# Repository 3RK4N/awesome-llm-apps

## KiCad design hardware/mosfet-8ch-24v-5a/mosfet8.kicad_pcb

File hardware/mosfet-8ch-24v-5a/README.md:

# 8 Kanal 24 V PNP MOSFET Çıkış Kartı (NPN/PNP girişli, DIN ray)

PLC / kontrol kartı çıkışlarını yükselten, opto-izoleli 8 kanallı high-side
(PNP, kaynak tipi) MOSFET kartı. Her giriş kendi çıkışını sürer; kartta işlemci yoktur.

## Özellikler

| | |
|---|---|
| Besleme | 24 V DC (19–30 V) |
| Çıkış | 8 × 24 V PNP, kanal başına 5 A sürekli |
| Toplam akım | 20 A (70 µm / 2 oz bakır ile); 35 µm bakırda 12 A ile sınırlayın |
| Giriş | 8 × 24 V, JP1 ile NPN veya PNP; ~3,7 mA @ 24 V, açma eşiği yaklaşık 7–9 V |
| İzolasyon | Giriş–çıkış arası optokuplör (JP1 takılı değilken ve `COM` ayrı beslenirken) |
| Koruma | Kanal başına 7 A hızlı SMD sigorta, serbest geçiş diyodu, kapı zeneri; beslemede TVS |
| Gösterge | Kanal başına yeşil LED (kapı sürülürken yanar), mavi besleme LED'i |
| PCB | 62 × 72 mm, 2 katman, tek yüz SMD dizgi |
| Montaj | 72 mm PCB genişliğine uygun DIN ray taşıyıcı (UM72 tipi profil); rayda 62 mm yer kaplar |
| Anahtarlama | Aç/kapa kullanım, en fazla ~20 Hz (PWM için uygun değildir) |

## Bağlantı

- **J3 (üst sağ):** soldan sağa `+24V +24V 0V 0V`. Toplam akım 12 A'yı geçiyorsa iki `+24V` kutbunu da kullanın.
- **J1 (üst sol):** soldan sağa `IN1 … IN8, COM`.
- **J2 (alt):** soldan sağa `OUT1 … OUT8`. Yük `OUTn` ile 0 V arasına bağlanır.
- **JP1:**
  - 1-2 (üst): **NPN** giriş — `COM` = +24 V, giriş 0 V'a çekilince kanal açılır.
  - 2-3 (alt): **PNP** giriş — `COM` = 0 V, girişe +24 V gelince kanal açılır.
  - Jumper yok: `COM` klemensine harici ortak uç bağlanır, giriş tarafı tam izole olur.

## Kanal devresi

```
IN ─ 4k7 ─┬─ opto LED (çift yönlü) ─ COM        +24V ─┬─ 10k ─┬─ ZD 15V ─┐
          └─ 1k ────────────────────┘                 │       │          │
                                                      S     kapı ────────┘
 opto C ─ LED ─ 10k ─ kapı        opto E ─ 0V       P-MOSFET
                                                      D ─ sigorta 7A ─┬─ OUT
                                                                      └─ SS36 ─ 0V
```

24 V'ta kapı gerilimi yaklaşık −11 V olur. SUD50P06-15 için iletim direnci en fazla
15 mΩ (25 °C); 5 A'da kanal başına yaklaşık 0,4–0,6 W ısı çıkar.

## Dosyalar

| Dosya | İçerik |
|---|---|
| `mosfet8.kicad_pro / .kicad_sch / .kicad_pcb` | KiCad 7 projesi (şema + PCB) |
| `mosfet8-schematic.pdf` | Şema çıktısı |
| `bom.csv` | Malzeme listesi (18 kalem, 88 parça) |
| `gerber/` | Gerber, delik (Excellon) ve dizgi konum dosyaları |
| `docs/` | PCB önizleme görselleri |
| `scripts/` | Şemayı ve PCB'yi üreten betikler |

Tasarım `scripts/design.py` içindeki tek bir bağlantı tablosundan üretilir. Yeniden üretmek için
(KiCad 7 kurulu Linux'ta):

```bash
cd scripts
python3 gen_sch.py && /usr/bin/python3 gen_pcb.py && python3 gen_bom.py
```

KiCad'de elle düzenleme yaparsanız betikleri tekrar çalıştırmayın; dosyaların üzerine yazar.

## Doğrulama durumu

- Şemadan çıkarılan netlist, bağlantı tablosuyla birebir eşleşiyor (60 net, 88 parça).
- KiCad 7.0.11 DRC: açıklık, kısa devre ve bağlanmamış pad hatası yok. Kalan 88 uyarı,
  betiğin çalıştığı ortamda kılıf kütüphane tablosu olmamasından kaynaklanır.
- ERC çalıştırılmadı (KiCad 7 komut satırında yok); projeyi açınca bir kez ERC çalıştırın.
- **Prototip üretilmedi ve test edilmedi.** Isıl değerler hesap tahminidir.

## Üretimden önce kontrol edilecekler

1. **Parça numaraları** hafızadan yazıldı. Siparişten önce datasheet'ten kılıf, pin sırası ve
   değerleri doğrulayın; özellikle Q (DPAK: 1 = G, tab = D, 3 = S) ve optokuplör (SO-4: 1-2 LED, 3 = E, 4 = C).
2. **Bakır kalınlığı:** 70 µm (2 oz) sipariş edin. 35 µm ile toplam akımı 12 A'da tutun.
3. **Kısa devre:** MOSFET'in kendi akım sınırlaması yoktur; koruma sigortaya ve güç kaynağının
   akım sınırına dayanır. Sigorta atınca değiştirilmesi gerekir (lehimli).
4. **Kanal LED'i** kapının sürüldüğünü gösterir; sigorta atmışsa LED yanar ama çıkış gelmez.
5. **Taşıyıcı:** PCB'de montaj deliği yoktur; kenardan tutan profil taşıyıcı varsayıldı.
   Seçtiğiniz taşıyıcının kenar payını (kenarda en yakın parça ~0,9 mm) kontrol edin.
6. **Klemensler** Phoenix PT 1,5 (3,5 mm) ve MKDS (5,08 mm) ayak izleridir; muadil kullanacaksanız
   ayak aralığı ve pin çapını karşılaştırın.

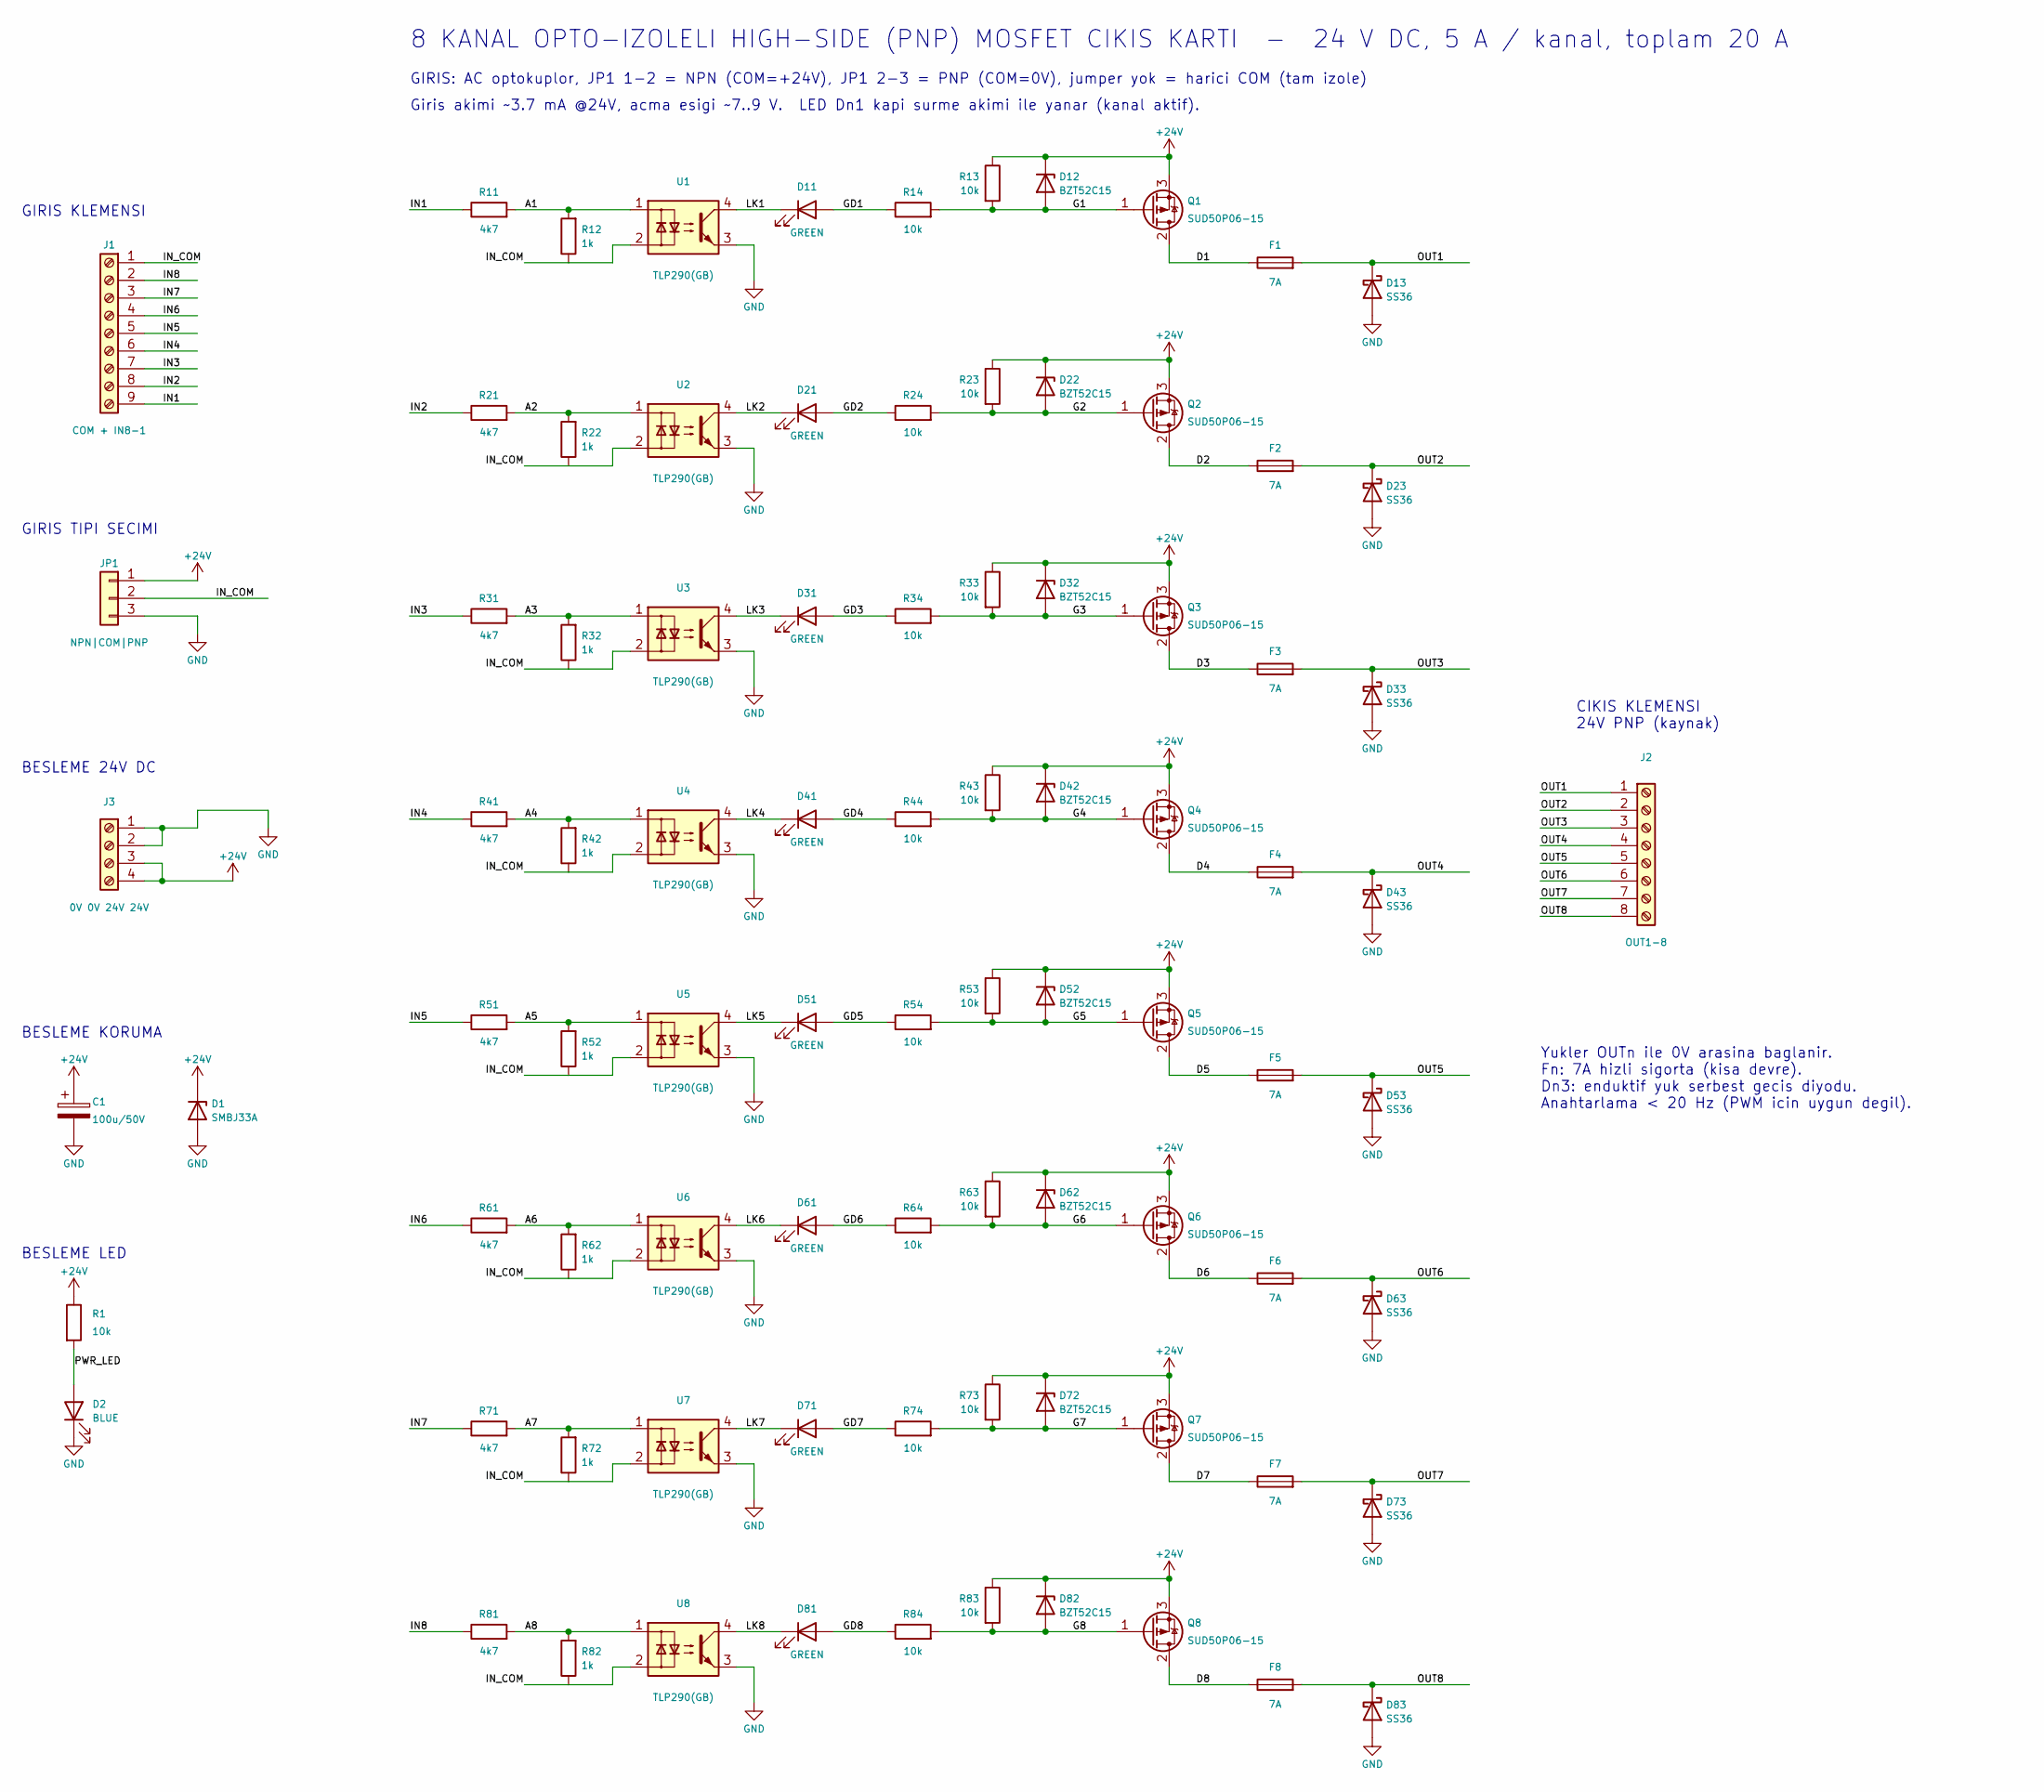
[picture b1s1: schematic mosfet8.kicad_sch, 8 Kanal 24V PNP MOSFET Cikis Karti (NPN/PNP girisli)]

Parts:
C1: 100u/50V; CP_Elec_8x10; MPN EEE-FK1H101P
D1: SMBJ33A; D_SMB; MPN SMBJ33A
D2: BLUE; LED_0603_1608Metric; MPN KP-1608QBC-D / 19-217/BHC
D11, D21, D31, D41, D51, D61, D71, D81: GREEN; LED_0603_1608Metric; MPN KP-1608SGC / 19-217/GHC
D12, D22, D32, D42, D52, D62, D72, D82: BZT52C15; D_SOD-123; MPN BZT52C15-7-F
D13, D23, D33, D43, D53, D63, D73, D83: SS36; D_SMA; MPN SS36
F1, F2, F3, F4, F5, F6, F7, F8: 7A; Fuse_Littelfuse-NANO2-451_453; MPN 0451007.MRL
J1: COM + IN8-1; TerminalBlock_Phoenix_PT-1,5-9-3.5-H_1x09_P3.50mm_Horizontal; MPN PT 1,5/9-3,5-H (1984688)
J2: OUT1-8; TerminalBlock_Phoenix_MKDS-1,5-8-5.08_1x08_P5.08mm_Horizont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; MPN MKDS 1,5/8-5,08 (1715786)
J3: 0V 0V 24V 24V; TerminalBlock_Phoenix_MKDS-3-4-5.08_1x04_P5.08mm_Horizontal; MPN MKDS 3/4-5,08 (1711741)
JP1: NPN|COM|PNP; PinHeader_1x03_P2.54mm_Vertical; MPN Pin header 1x3 2.54mm + jumper
Q1, Q2, Q3, Q4, Q5, Q6, Q7, Q8: SUD50P06-15; TO-252-2; MPN SUD50P06-15-GE3
R1, R13, R14, R23, R24, R33, R34, R43, R44, R53, R54, R63, R64, R73, R74, R83, R84: 10k; R_0603_1608Metric; MPN RC0603FR-0710KL
R11, R21, R31, R41, R51, R61, R71, R81: 4k7; R_1206_3216Metric; MPN RC1206FR-074K7L
R12, R22, R32, R42, R52, R62, R72, R82: 1k; R_0603_1608Metric; MPN RC0603FR-071KL
U1, U2, U3, U4, U5, U6, U7, U8: TLP290(GB); SOP-4_4.4x2.6mm_P1.27mm; MPN TLP290(GB-TP,SE

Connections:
+24V: C1.1, D1.1 (K), D12.1 (K), D22.1 (K), D32.1 (K), D42.1 (K), D52.1 (K), D62.1 (K), D72.1 (K), D82.1 (K), J3.3, J3.4, JP1.1, Q1.3 (S), Q2.3 (S), Q3.3 (S), Q4.3 (S), Q5.3 (S), Q6.3 (S), Q7.3 (S), Q8.3 (S), R1.1, R13.1, R23.1, R33.1, R43.1, R53.1, R63.1, R73.1, R83.1
/A1: R11.2, R12.2, U1.1
/A2: R21.2, R22.2, U2.1
/A3: R31.2, R32.2, U3.1
/A4: R41.2, R42.2, U4.1
/A5: R51.2, R52.2, U5.1
/A6: R61.2, R62.2, U6.1
/A7: R71.2, R72.2, U7.1
/A8: R81.2, R82.2, U8.1
/D1: F1.1, Q1.2 (D)
/D2: F2.1, Q2.2 (D)
/D3: F3.1, Q3.2 (D)
/D4: F4.1, Q4.2 (D)
/D5: F5.1, Q5.2 (D)
/D6: F6.1, Q6.2 (D)
/D7: F7.1, Q7.2 (D)
/D8: F8.1, Q8.2 (D)
/G1: D12.2 (A), Q1.1 (G), R13.2, R14.2
/G2: D22.2 (A), Q2.1 (G), R23.2, R24.2
/G3: D32.2 (A), Q3.1 (G), R33.2, R34.2
/G4: D42.2 (A), Q4.1 (G), R43.2, R44.2
/G5: D52.2 (A), Q5.1 (G), R53.2, R54.2
/G6: D62.2 (A), Q6.1 (G), R63.2, R64.2
/G7: D72.2 (A), Q7.1 (G), R73.2, R74.2
/G8: D82.2 (A), Q8.1 (G), R83.2, R84.2
/GD1: D11.2 (A), R14.1
/GD2: D21.2 (A), R24.1
/GD3: D31.2 (A), R34.1
/GD4: D41.2 (A), R44.1
/GD5: D51.2 (A), R54.1
/GD6: D61.2 (A), R64.1
/GD7: D71.2 (A), R74.1
/GD8: D81.2 (A), R84.1
/IN1: J1.9, R11.1
/IN2: J1.8, R21.1
/IN3: J1.7, R31.1
/IN4: J1.6, R41.1
/IN5: J1.5, R51.1
/IN6: J1.4, R61.1
/IN7: J1.3, R71.1
/IN8: J1.2, R81.1
/IN_COM: J1.1, JP1.2, R12.1, R22.1, R32.1, R42.1, R52.1, R62.1, R72.1, R82.1, U1.2, U2.2, U3.2, U4.2, U5.2, U6.2, U7.2, U8.2
/LK1: D11.1 (K), U1.4
/LK2: D21.1 (K), U2.4
/LK3: D31.1 (K), U3.4
/LK4: D41.1 (K), U4.4
/LK5: D51.1 (K), U5.4
/LK6: D61.1 (K), U6.4
/LK7: D71.1 (K), U7.4
/LK8: D81.1 (K), U8.4
/OUT1: D13.1 (K), F1.2, J2.1
/OUT2: D23.1 (K), F2.2, J2.2
/OUT3: D33.1 (K), F3.2, J2.3
/OUT4: D43.1 (K), F4.2, J2.4
/OUT5: D53.1 (K), F5.2, J2.5
/OUT6: D63.1 (K), F6.2, J2.6
/OUT7: D73.1 (K), F7.2, J2.7
/OUT8: D83.1 (K), F8.2, J2.8
/PWR_LED: D2.2 (A), R1.2
GND: C1.2, D1.2 (A), D2.1 (K), D13.2 (A), D23.2 (A), D33.2 (A), D43.2 (A), D53.2 (A), D63.2 (A), D73.2 (A), D83.2 (A), J3.1, J3.2, JP1.3, U1.3, U2.3, U3.3, U4.3, U5.3, U6.3, U7.3, U8.3

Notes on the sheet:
8 KANAL OPTO-IZOLELI HIGH-SIDE (PNP) MOSFET CIKIS KARTI - 24 V DC, 5 A / kanal, toplam 20 A
GIRIS: AC optokuplor, JP1 1-2 = NPN (COM=+24V), JP1 2-3 = PNP (COM=0V), jumper yok = harici COM (tam izole)
Giris akimi ~3.7 mA @24V, acma esigi ~7..9 V. LED Dn1 kapi surme akimi ile yanar (kanal aktif).
GIRIS KLEMENSI
GIRIS TIPI SECIMI
BESLEME 24V DC
BESLEME KORUMA
BESLEME LED
CIKIS KLEMENSI 24V PNP (kaynak)
Yukler OUTn ile 0V arasina baglanir. Fn: 7A hizli sigorta (kisa devre). Dn3: enduktif yuk serbest gecis diyodu. Anahtarlama < 20 Hz (PWM icin uygun degil).

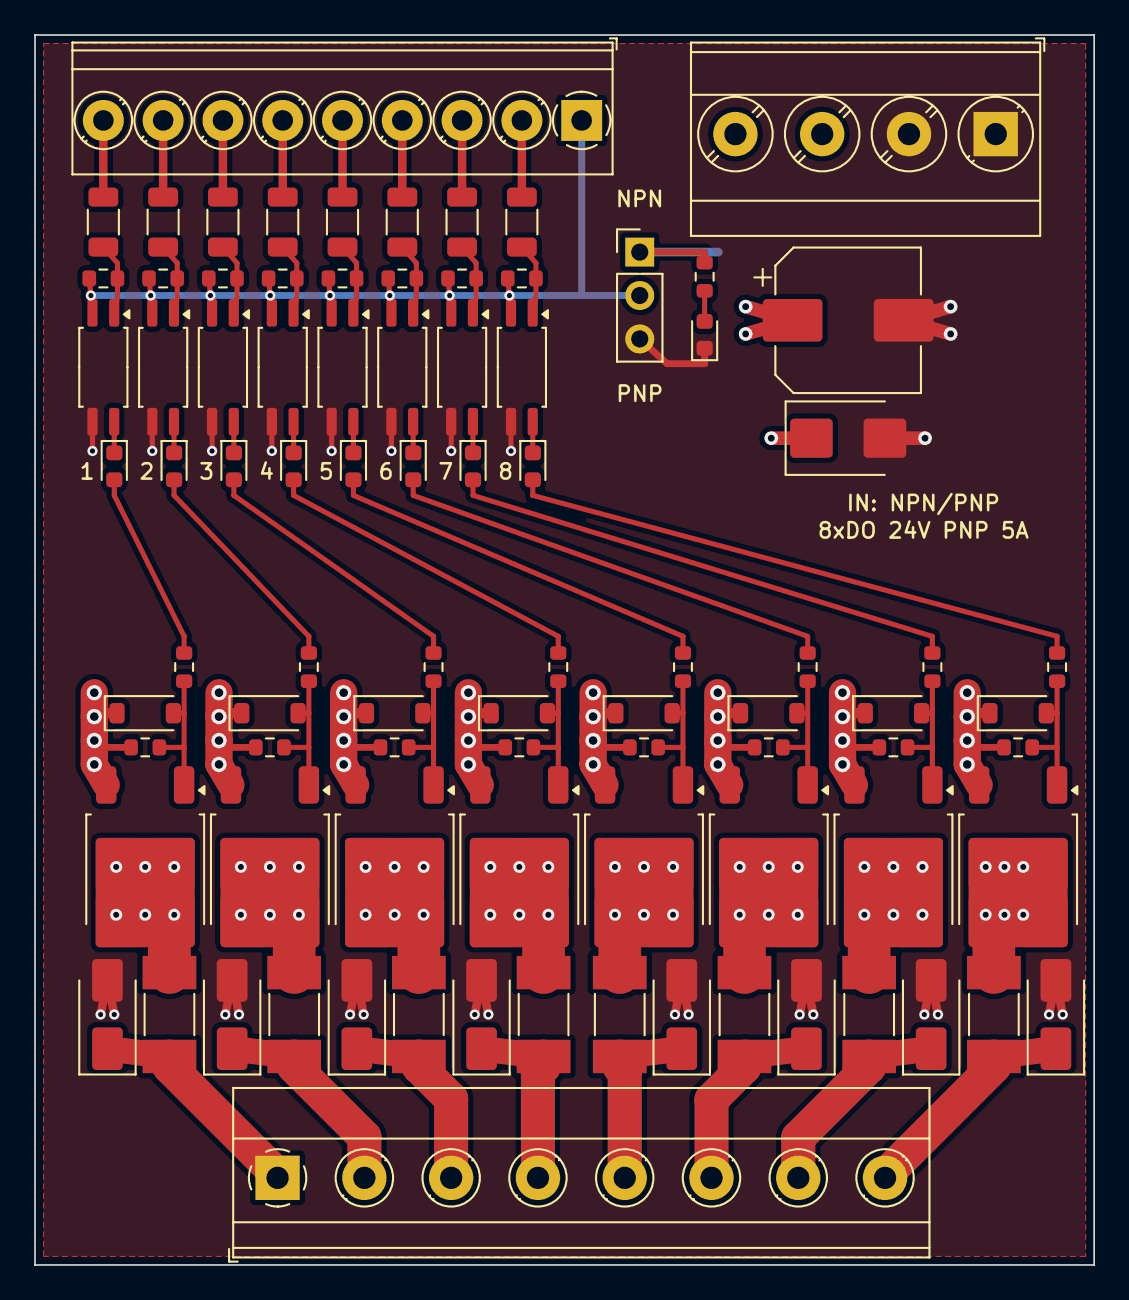
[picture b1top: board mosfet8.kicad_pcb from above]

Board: 2 copper layers, 62.0 x 72.0 mm, 88 parts (0 on the bottom side), 60 nets.

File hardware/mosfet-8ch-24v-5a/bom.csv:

Adet,Referanslar,Deger,Kilif,Onerilen parca (MPN),Aciklama
1,C1,100u/50V,CP_Elec_8x10,EEE-FK1H101P,Elektrolitik 100uF 50V SMD 8x10
1,D1,SMBJ33A,D_SMB,SMBJ33A,TVS 33V 600W tek yonlu SMB
1,D2,BLUE,LED_0603_1608Metric,KP-1608QBC-D / 19-217/BHC,Besleme LED mavi 0603
8,D11 D21 D31 D41 D51 D61 D71 D81,GREEN,LED_0603_1608Metric,KP-1608SGC / 19-217/GHC,Kanal durum LED yesil 0603
8,D12 D22 D32 D42 D52 D62 D72 D82,BZT52C15,D_SOD-123,BZT52C15-7-F,Kapi koruma zeneri 15V SOD-123
8,D13 D23 D33 D43 D53 D63 D73 D83,SS36,D_SMA,SS36,Serbest gecis diyodu 3A 60V SMA
8,F1 F2 F3 F4 F5 F6 F7 F8,7A,Fuse_Littelfuse-NANO2-451_453,0451007.MRL,"SMD sigorta 7A hizli, Littelfuse Nano2 451"
1,J1,COM + IN8-1,"TerminalBlock_Phoenix_PT-1,5-9-3.5-H_1x09_P3.50mm_Horizontal","PT 1,5/9-3,5-H (1984688)",Giris klemensi 9 kutup 3.5mm
1,J2,OUT1-8,"TerminalBlock_Phoenix_MKDS-1,5-8-5.08_1x08_P5.08mm_Horizontal","MKDS 1,5/8-5,08 (1715786)",Cikis klemensi 8 kutup 5.08mm
1,J3,0V 0V 24V 24V,TerminalBlock_Phoenix_MKDS-3-4-5.08_1x04_P5.08mm_Horizontal,"MKDS 3/4-5,08 (1711741)",Besleme klemensi 4 kutup 5.08mm 24A
1,JP1,NPN|COM|PNP,PinHeader_1x03_P2.54mm_Vertical,Pin header 1x3 2.54mm + jumper,"Giris tipi secimi: 1-2 NPN (COM=+24V), 2-3 PNP (COM=0V)"
8,Q1 Q2 Q3 Q4 Q5 Q6 Q7 Q8,SUD50P06-15,TO-252-2,SUD50P06-15-GE3,"P-MOSFET -60V 15mOhm DPAK (alt: SQD50P06-15L, NCE60P50K)"
1,R1,10k,R_0603_1608Metric,RC0603FR-0710KL,Besleme LED direnci 10k 0603
8,R11 R21 R31 R41 R51 R61 R71 R81,4k7,R_1206_3216Metric,RC1206FR-074K7L,Giris seri direnci 4k7 1% 0.25W 1206
8,R12 R22 R32 R42 R52 R62 R72 R82,1k,R_0603_1608Metric,RC0603FR-071KL,Opto LED paralel direnci 1k 1% 0603
8,R13 R23 R33 R43 R53 R63 R73 R83,10k,R_0603_1608Metric,RC0603FR-0710KL,Kapi-kaynak direnci 10k 1% 0603
8,R14 R24 R34 R44 R54 R64 R74 R84,10k,R_0603_1608Metric,RC0603FR-0710KL,Kapi seri direnci 10k 1% 0603
8,U1 U2 U3 U4 U5 U6 U7 U8,TLP290(GB),SOP-4_4.4x2.6mm_P1.27mm,"TLP290(GB-TP,SE","AC girisli optokuplor SO-4, CTR>=100% (alt: LTV-354T, EL354N)"
